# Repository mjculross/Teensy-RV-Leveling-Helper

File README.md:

# Teensy-RV-Leveling-Helper
Teensy RV Leveling Helper using Teensy 4.0 + BMA400 Triple Axis Accelerometer Breakout + ILI9341 Color 320x240 TFT Touchscreen display + NRF24L01 radio

This project came about after we acquired a used RV motorhome & I quickly grew tired of the following process of attempting to level the RV:
   1) park the RV on a particular site
   2) look at the bubble level on the kitchen counter to determine "level or not"
   3) make/revise my best guess as to how many blocks are required on each wheel to attain "level"
   4) drive the RV up on the best guess number of blocks
   5) if the RV is "level", then you're DONE !!
   6) if the RV is not yet "level", then drive the RV down off of the best guess number of blocks
   7) goto 3) above & repeat several times (until either we're close enough, or I get fed up, whichever comes first)

Using the TRLH makes this process much more convenient & quick as follows:
   1) park your RV where you want it to ultimately rest for the duration of your stay
   2) apply power to the inside TRLH & place it on the kitchen counter inside the RV
      (which provides a non-moving reference plane for the entire RV)
   3) if you are using a second TRLH as a remote display, apply power to the remote TRLH
      (the two units will establish sync over the radio & the remote unit will ignore its
      own accelerometer data, and will instead perform all leveling calculations using
      the accelerometer data received from the inside TRLH over the NRF24L01 radio -
      NOTE: if you're not using the remote TRLH, the inside TRLH will still operate as a
      single unit)
   4) take note of the leveling solution displayed (indicating results of calculating
      how many inches to raise any of the wheels in order to bring the RV to a perfectly
      level position)
   5) back the RV away sufficiently to leave room to put the ramps into place
   6) build and place the required ramps (using 1" blocks) to raise the wheels as indicated
   7) drive the RV up onto the newly built leveling ramps
   8) verify that the TRLH now shows 0" for each wheel - LEVELING SUCCESS !! (Note that
      anything within 1" of level is sufficient for the comfort of the occupants, as
      well as for the equipment, primarily the refrigerator)
   9) sit back & enjoy a cold drink of your choice

This project incorporates the following:

   HARDWARE:

      Teensy 4.0
         available from PJRC.com https://www.pjrc.com/teensy-4-0/

      ILI9341 Color 320x240 TFT Touchscreen display
         available from PJRC.com https://www.pjrc.com/store/display_ili9341_touch.html

      HiLetgo NRF24L01+ Wireless Transceiver Module 2.4GHz
         available from https://www.amazon.com/gp/product/B00LX47OCY
  
      BMA400 Triple Axis Accelerometer Breakout
         available from Sparkfun https://www.sparkfun.com/products/21208

      PowerBoost 1000 Charger - Rechargeable 5V Lipo USB Boost @ 1A - 1000C
         available from Adafruit https://www.adafruit.com/product/2465
         
      Lithium Ion Polymer Battery - 3.7v 2500mAh
         available from Adafruit https://www.adafruit.com/product/328

   This project uses touchscreen input & color display to create a visual (graphical) indication of how many inches of leveling blocks are required to be put under each wheel of an RV to level it
  
   This project uses the ILI9341_t3 library, which has been optimized for use with the Teensy TFT display, as well as the XPT2046_Touchscreen.h touchscreen library for that same display

   This project (optionally) uses the NRF24L01 wireless transceiver module to allow two TRLH units to communicate, using one as the inside unit taking measurements, and the other as a remote display
   
   This project specifically uses the SparkFun BMA400 support library (SparkFun_BMA400_Arduino_Library.h) which can be added using the Arduino IDE library manager.

   This project allows & stores configurable wheel base (front to back wheels distance) from 60" to 255".

   This project allows & stores configurable wheel distance (front wheels, left to right distance) from 60" to 84".

   Internet reference (with equation derivation) for transforming accelerometer x,y,z vector data into pitch & roll angles:

      https://mwrona.com/posts/accel-roll-pitch/

   The specific DPDT switch that I use for power control (& for which the 3D printed case is designed) is the Carling Technologies 62115929-0-0-V, available from digikey as part number 432-1252-ND (https://www.digikey.com/en/products/detail/carling-technologies/62115929-0-0-V/3025077).

   An Adafruit microUSB panel mount extension cable Product ID 3258 (https://www.adafruit.com/product/3258) is mounted on the side wall of the case.  The cable is split such that the USB 5VDC line connects to the USB input pin on the Adafruit PowerBoost 1000C to provide power & battery charging, while the remaining GROUND, D-, & D+ signals connect to the microUSB connector on the Teensy to allow (re)programming without opening the case.

   This project implements the following:

      1) read the XYZ vector from the BMA400 triple axis accelerometer breakout
      2) use the XYZ vector to calculate PITCH and ROLL values for the current plane of the RV/trailer orientation
      3) use the calculated PITCH and ROLL values to determine the highest wheel/point (which will not require any blocks)
      4) use the calculated PITCH and ROLL values to determine the number of inches of blocks required for the remaining wheels/points to achieve "level"
      5) update the display with the current results once per second (& average all values otherwise)
      6) repeat

UPDATE NOTES for version 1.6 dated 07/20/2024 @0635:

   Updated TRAILER MODE such that is now indicates LOWER or RAISE values up to 24" for the
   hitch, and RAISE values up to 12" for the wheels.
   
UPDATE NOTES for version 1.4 dated 04/05/2024 @1335:

   Now, two units can be used & they talk to each other using NRF24L01 wireless modules.
   The first unit powered on will assume that it is the "INSIDE" unit (which is actually
   reading its onboard BMA400 accelerometer & displaying the leveling recommendations from
   the calculated pitch & roll).  The second unit will assume that it is the "OUTSIDE" unit
   (which is ignoring its onboard BMA400, and is instead displaying the leveling
   recommendations calculated using the pitch & roll data received over the NRF24L01
   wireless link from the "INSIDE" unit).  This way, leveling can be achieved without the
   need for running back & forth between inside (to look at the Teensy-RV-Leveling-Helper)
   & outside (to make adjustments).  Any unit can also be used by itself...it does not have
   to have a partner to work.  The latest firmware also automatically detects the lack of
   the NRF24L01 module & operates successfully without the radio as a standalone unit.

   EASTER EGG: If you hold down on the battery status display box for 5-seconds, the unit
   will change from RV LEVELING MODE to LED COLOR CONTROLLER MODE.  In this mode, with a
   WS2812B LED strip powered from the 5VDC supply & common ground with the Teensy, tie the
   data line to PIN 8 & the RV Leveling Helper can also be used to create custom LED
   patterns, with the ability to control the mode (MARQUIS, CYCLE, FADE, CROSSFADE, ZIPPER,
   & RANDOM), the brightness, the radio power level (for using another unit as a remote
   control), the radio channel (to put the LED COLOR CONTROLLER MODE on a different radio
   channel from the RV LEVELING MODE to minimize interference between them).  Up to ten
   different custom patterns can be stored in EEPROM for quick recall.  Each pattern can
   be from two to thirty-two LEDs in length.  Each LED can be set to any of over sixteen
   million colors.  You can also customize the speed for each pattern individually, as
   well as the direction of movement (FORWARD / REVERSE).  An RV Leveling Helper which
   is being operated in LED COLOR CONTROLLER MODE need not have the TFT Color Touchscreen
   installed/connected.  By shorting PIN 10 on the Teensy to ground, an RV Leveling
   Helper unit can be forced into LED COLOR CONTROLLER MODE (specifically for the case
   where you have an RV Leveling helper unit that does not have a display connected by
   which to change between the two modes, essentially making it a dedicated, stand-alone
   LED COLOR CONTROLLER).  For the RV Leveling Helper with a TFT Color Touchscreen
   installed/connected and operting in the LED COLOR CONTROLLER MODE, holding down on
   the battery display box for 5-seconds will change it back to RV LEVELING MODE.  So,
   you now have two-controllers-in-one with this new capability.
   
RV LEVELING CONTROLLER OPERATIONAL MODE:

   This project can be switched between the following primary modes of operation:
   - RV mode (four points of balance/leveling = four wheels)
   - Trailer mode (three points of balance/leveling = two wheels and the hitch)
   - Bubble mode (traditional 2-D bubble level)

MECHANICAL ASSEMBLY & CALIBRATION:

   For information on mechanical assembly and/or calibration, see the "readme" file in the "photos" folder.

ORDERING INFO:

   The compact PCB is available from OshPark here: https://oshpark.com/projects/CN9rpz97/order

CONTACT INFO:

If you have any questions, suggestions for improvement, and most especially any bug reports, please contact me at kd5rxt@arrl.net

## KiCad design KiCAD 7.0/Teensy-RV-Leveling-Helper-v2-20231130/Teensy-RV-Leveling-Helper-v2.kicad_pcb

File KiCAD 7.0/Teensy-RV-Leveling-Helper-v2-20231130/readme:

This set of KiCAD design files is for the updated v2 (compact 3.0" x 3.8") PCB for the 20231130 version of the Teensy-RV-Leveling-Helper.

The included schematic includes external connection points as follows (with connectivity description in parentheses):
- USB VIN (input 5VDC from the external USB connector)
- DISABLE IN (use an external switch to connect the EN input on the Adafruit PowerBoost 1000C to GROUND to deactivate the project)

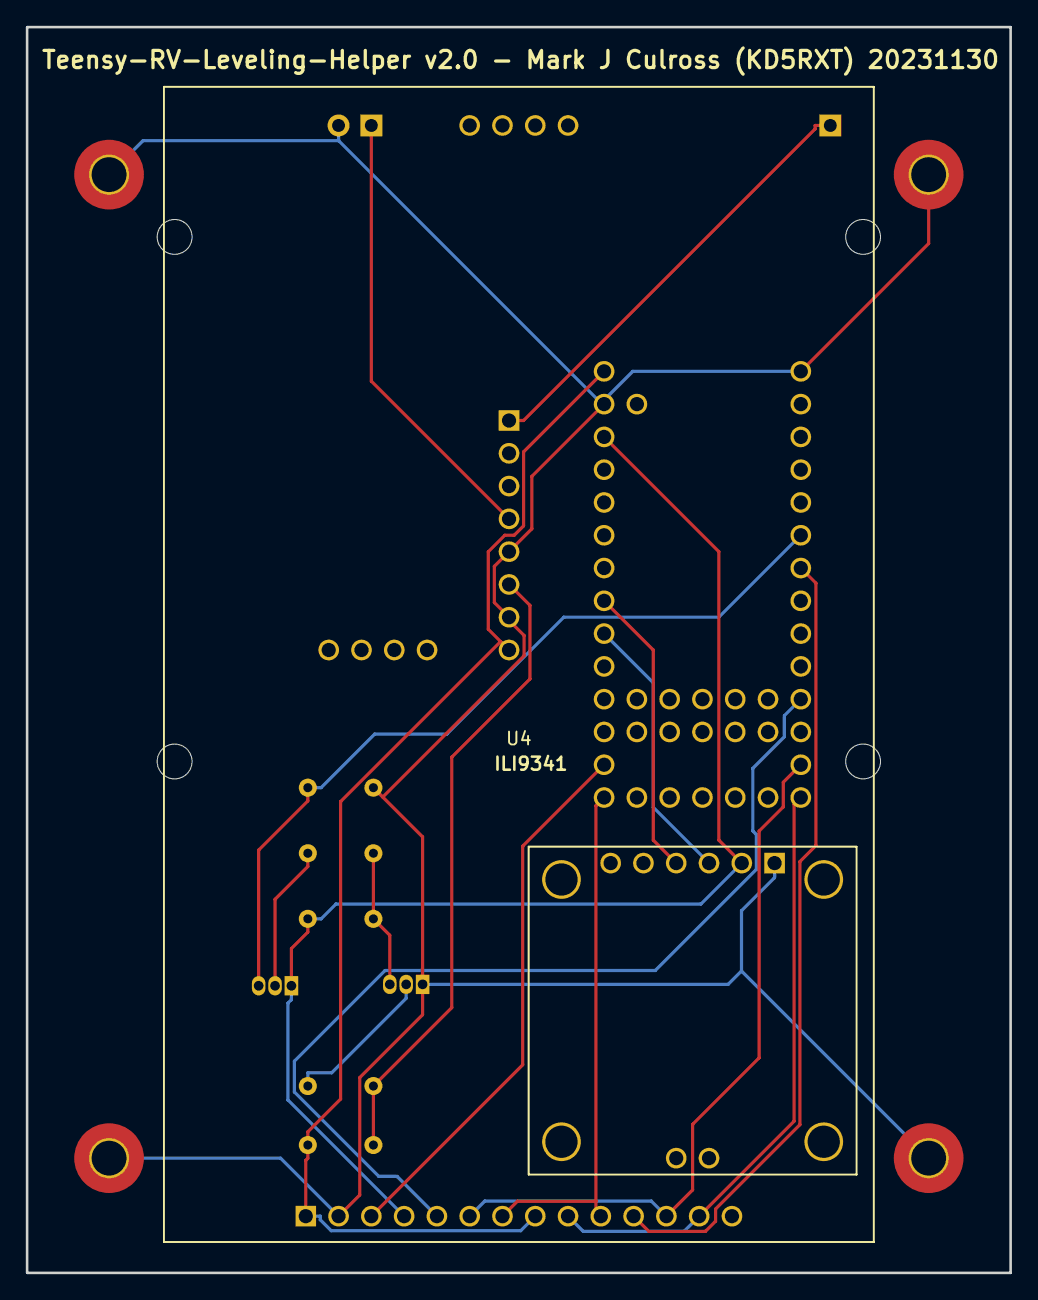
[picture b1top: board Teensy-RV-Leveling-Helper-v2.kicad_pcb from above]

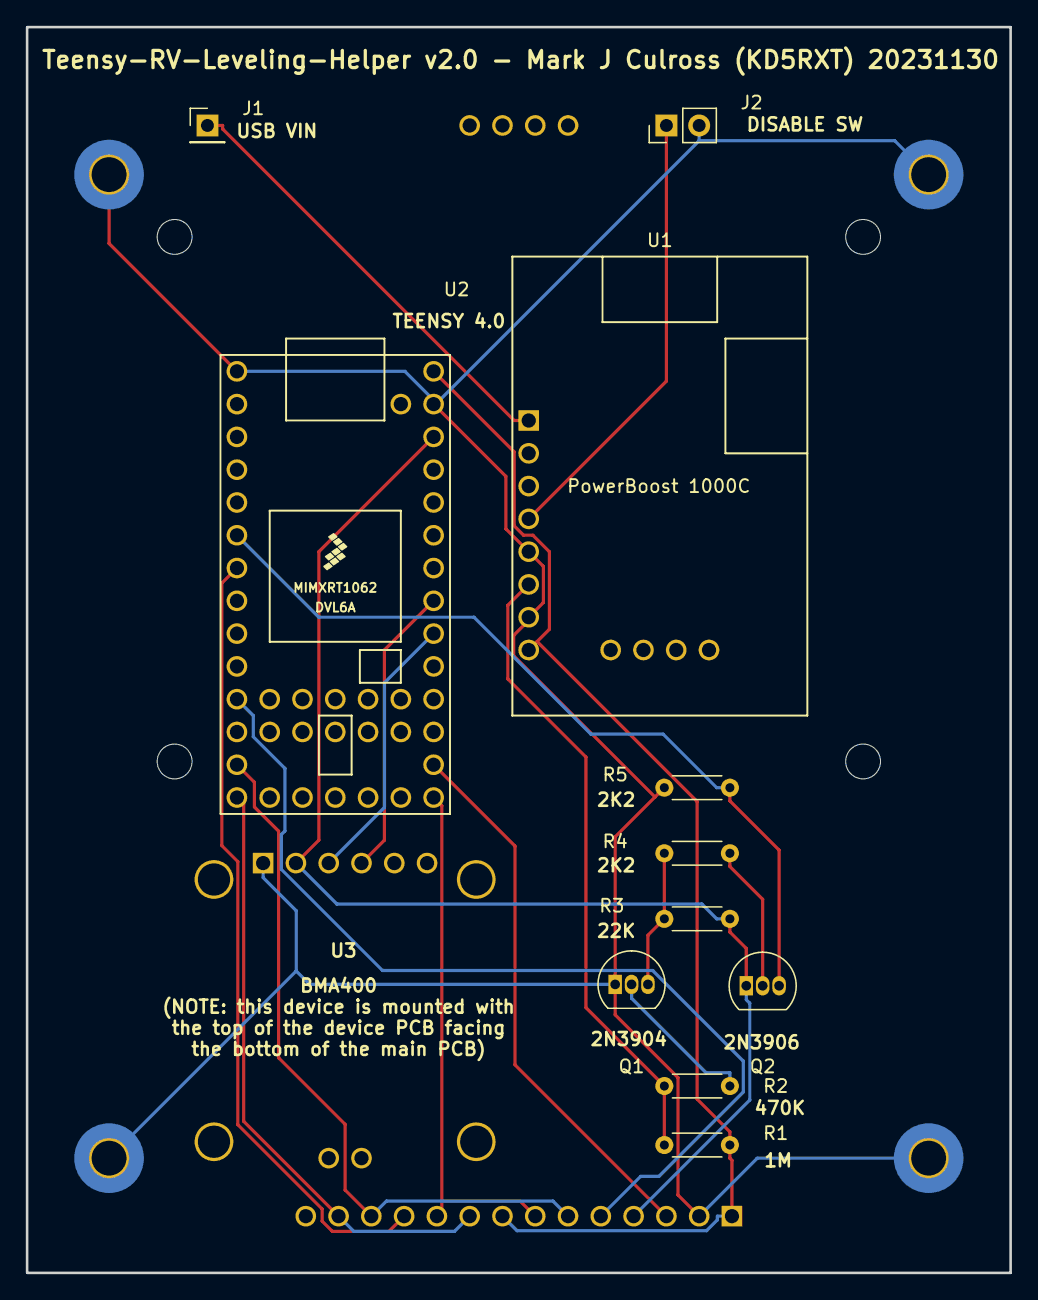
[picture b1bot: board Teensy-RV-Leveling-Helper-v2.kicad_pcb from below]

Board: 2 copper layers, 76.2 x 96.5 mm, 21 parts (11 on the bottom side), 18 nets.

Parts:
H1: BATT-a; MountingHole_2.7mm
H2: BATT-b; MountingHole_2.7mm
H3: BATT-c; MountingHole_2.7mm
H4: BATT-d; MountingHole_2.7mm
H5: PCB-a; MountingHole_2.7mm_M2.5_Pad_TopBottom
H6: PCB-b; MountingHole_2.7mm_M2.5_Pad_TopBottom
H7: PCB-c; MountingHole_2.7mm_M2.5_Pad_TopBottom
H8: PCB-d; MountingHole_2.7mm_M2.5_Pad_TopBottom
J1: USB VIN; PinHeader_1x01_P2.54mm_Vertical
J2: DISABLE SW; PinHeader_1x02_P2.54mm_Vertical
Q1: 2N3904; TO-92_Inline
Q2: 2N3906; TO-92_Inline
R1: 1M; R_Axial_DIN0204_L3.6mm_D1.6mm_P5.08mm_Horizontal
R2: 470K; R_Axial_DIN0204_L3.6mm_D1.6mm_P5.08mm_Horizontal
R3: 22K; R_Axial_DIN0204_L3.6mm_D1.6mm_P5.08mm_Horizontal
R4, R5: 2K2; R_Axial_DIN0204_L3.6mm_D1.6mm_P5.08mm_Horizontal
U1: Powerboost1000C; PowerBoost1000C
U2: Teensy4.0; Teensy40
U3: BMA400
U4: Teensy ILI9341; ILI9341

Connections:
GNDREF: H5.1, H6.1, H7.1, H8.1, J2.2, Q1.1 (E), R5.1, U1.5 (GND), U1.7 (G), U2.1 (GND), U2.32 (GND), U3.1 (GND), U4.2 (GND)
unnamed: J1.1, U1.1 (USB)
unnamed: J2.1, U1.4 (EN)
unnamed: Q1.2 (B), R2.2
unnamed: Q1.3 (C), R3.1, R4.1
unnamed: Q2.2 (B), R4.2
unnamed: Q2.3 (C), R5.2, U2.6 (4_BCLK2)
unnamed: Q2.1 (E), R3.2, U2.31 (3V3), U3.2 (3V3), U4.4 (RESET)
unnamed: R1.2, U1.8 (5Vo), U2.33 (VIN), U4.1 (VCC), U4.8 (LED)
unnamed: R1.1, R2.1, U1.6 (LBO)
unnamed: U2.7 (5_IN2), U4.11 (T_CS)
unnamed: U2.11 (9_OUT1C), U4.5 (DC)
unnamed: U2.13 (11_MOSI_CTX1), U4.6 (SDI(MOSI)), U4.12 (T_DIN)
unnamed: U2.14 (12_MISO_MQSL), U4.9 (SDO(MISO)), U4.13 (T_DO)
unnamed: U2.20 (13_SCK_CRX1_LED), U4.7 (SCK), U4.10 (T_CLK)
unnamed: U2.21 (14_A0_TX3_SPDIF_OUT), U4.3 (CS)
unnamed: U2.25 (18_A4_SDA0), U3.3 (SDA/PICO)
unnamed: U2.26 (19_A5_SCL0), U3.4 (SCL/SCK)

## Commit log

2023-10-23 Update README.md
    add project details
2023-10-23 Create Teensy-RV-Leveling-helper.ino
    Version of Teensy-RV-Leveling-Helper.ino 1.0 dated 10/07/2023 @1745
2023-10-23 Create temp
2023-10-23 Add files via upload
    KiCAD 7.0 project with a simple schematic of the Teensy-RV-Leveling-Helper project.
2023-10-23 Create readme
    added description of the connections to the external DPDT Power Switch
2023-11-29 Add files via upload
    Updated to include new PCB
2023-11-29 code cleanup/update
2023-11-29 Create TRLH-v1
2023-11-30 added BUBBLE mode
2023-11-30 Create separate repositories for v1 & v2 PCBs
2023-12-24 added PCB ordering info
2023-12-24 corrected PCB ordering info
2023-12-24 updated PCB ordering info
2023-12-28 Updated firmware - now supports optional NRF24L01
    Now, two units can be used & they talk to each other using NRF24L01 wireless modules. The first unit powered on will assume that it is the "INSIDE" unit (which is actually reading its onboard BMA400 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
2023-12-28 Detail latest updates
2024-01-03 Updated to allow automatic button repeats
2024-01-03 Updated the calibration procedure for clarity
2024-04-23 Add files via upload
    version 1.3 dated 03/25/2024 @1940
2024-05-05 Updated to version 1.4 dated 20240504-1335
2024-05-05 Update README to include information on the new LED COLOR CONTROLLER MODE
2024-05-05 Instructions for using LED COLOR CONTROLLER MODE
2024-05-05 Update LICENSE
2024-05-05 Update to include info on LED COLOR CONTROLLER MODE
2024-07-30 Updated to version 1.6
    Enhances TRAILER MODE to indicate whether to raise or lower hitch.
2024-07-30 Updated for version 1.6
